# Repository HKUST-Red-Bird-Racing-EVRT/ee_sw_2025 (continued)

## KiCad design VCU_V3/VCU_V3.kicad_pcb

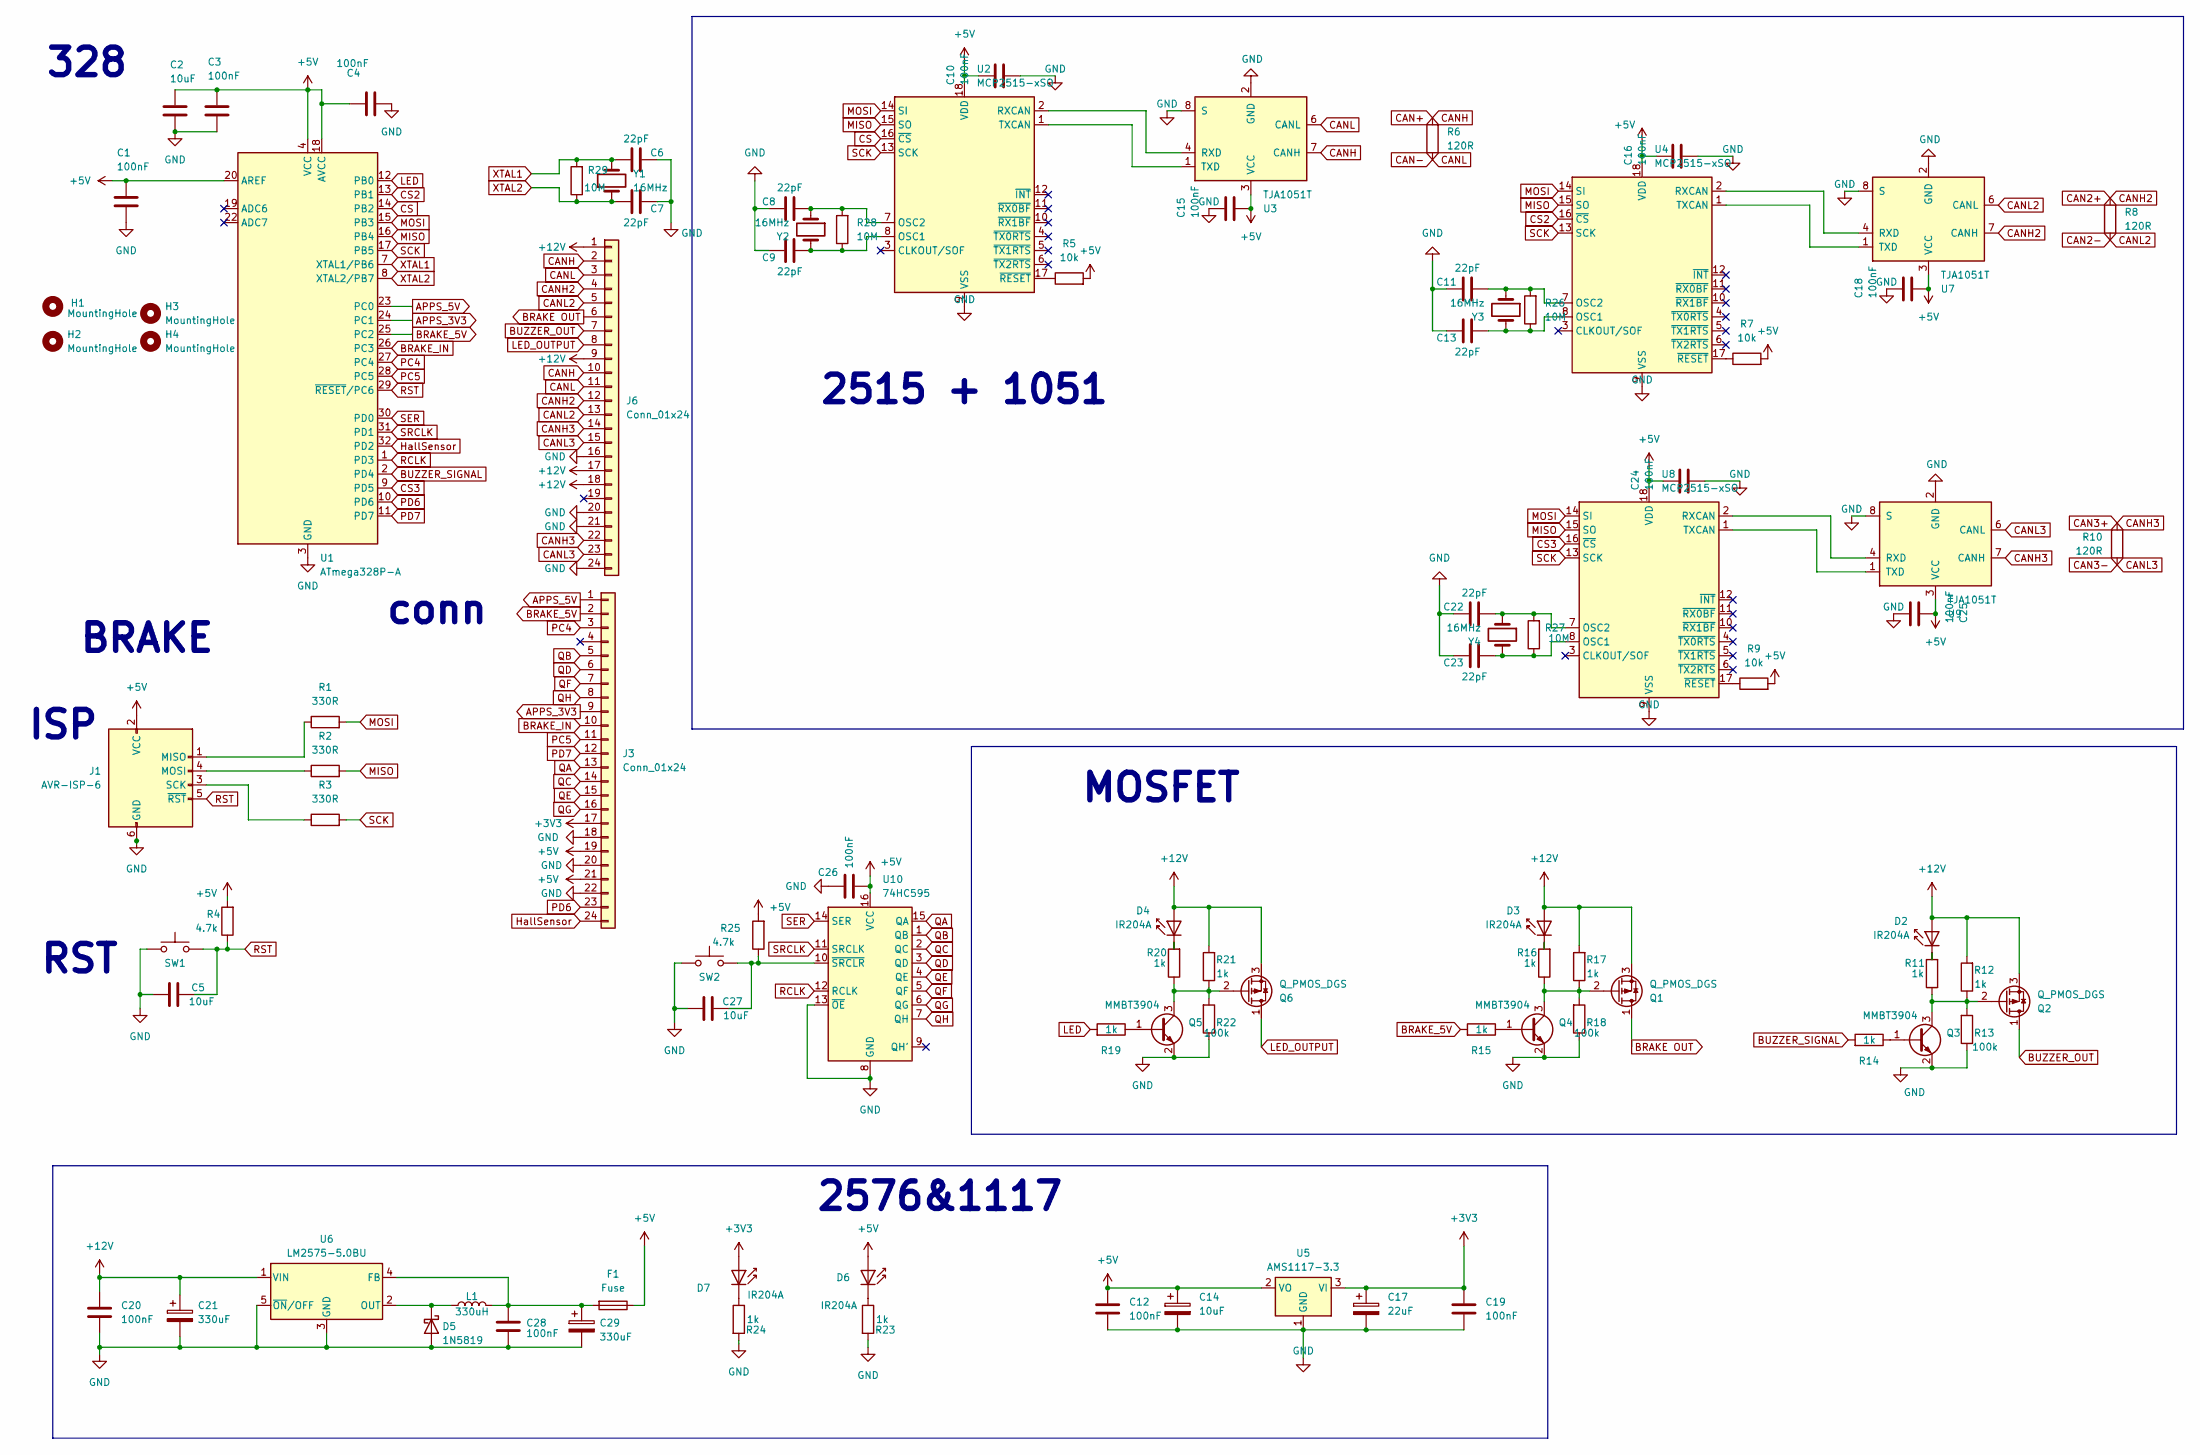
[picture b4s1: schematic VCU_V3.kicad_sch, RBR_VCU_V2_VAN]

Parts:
C1, C3, C4, C10, C12, C15, C16, C18, C19, C20, C24, C25, C26, C28: 100nF; C_0805_2012Metric_Pad1.18x1.45mm_HandSolder_L
C2, C5, C14, C27: 10uF; C_0805_2012Metric_Pad1.18x1.45mm_HandSolder_L
C6, C7, C8, C9, C11, C13, C22, C23: 22pF; C_0805_2012Metric_Pad1.18x1.45mm_HandSolder_L
C17: 22uF; C_0805_2012Metric_Pad1.18x1.45mm_HandSolder_L
C21, C29: 330uF; CP_Radial_D10.0mm_P5.00mm_F
D2, D3, D4, D6, D7: IR204A; LED_1206_3216Metric_Pad1.42x1.75mm_HandSolder
D5: 1N5819; D_SMA_Handsoldering
F1: Fuse; Fuse_1210_3225Metric_Pad1.42x2.65mm_HandSolder
H1, H2, H3, H4: MountingHole; MountingHole_3.2mm_M3
J1: AVR-ISP-6; PinHeader_2x03_P2.54mm_Vertical
J3, J6: Conn_01x24; HD241_24pin
L1: 330uH; L_10.4x10.4_H4.8
Q1, Q2, Q6: Q_PMOS_DGS; SOT-23
Q3, Q4, Q5: MMBT3904; SOT-23
R1, R2, R3: 330R; R_0805_2012Metric_Pad1.20x1.40mm_HandSolder_L
R4, R25: 4.7k; R_0805_2012Metric_Pad1.20x1.40mm_HandSolder_L
R5, R7, R9: 10k; R_0805_2012Metric_Pad1.20x1.40mm_HandSolder_L
R6, R8, R10: 120R; R_0805_2012Metric_Pad1.20x1.40mm_HandSolder_L
R11, R12, R14, R15, R16, R17, R19, R20, R21, R23, R24: 1k; R_0805_2012Metric_Pad1.20x1.40mm_HandSolder_L
R13, R18, R22: 100k; R_0805_2012Metric_Pad1.20x1.40mm_HandSolder_L
R26, R27, R28, R29: 10M; R_0805_2012Metric_Pad1.20x1.40mm_HandSolder_L
SW1, SW2: SW_Push; SW_PUSH_6mm_H5mm
U1: ATmega328P-A; TQFP-32_7x7mm_P0.8mm_L
U2, U4, U8: MCP2515-xSO; SOIC-18W_7.5x11.6mm_P1.27mm_L
U3, U7, U9: TJA1051T; SOIC-8_3.9x4.9mm_P1.27mm
U5: AMS1117-3.3; SOT-223-3_TabPin2
U6: LM2575-5.0BU; TO-263-5_TabPin3
U10: 74HC595; SOIC-16_3.9x9.9mm_P1.27mm
Y1, Y2, Y3, Y4: 16MHz; Crystal_HC49-U_Vertical_W_SMD

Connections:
+3V3: C17.1, C19.1, D7.2 (A), J3.17, U5.3 (VI)
+5V: C1.2, C2.2, C3.2, C4.2, C10.2, C12.1, C14.1, C15.1, C16.2, C18.1, C24.2, C25.2, C26.1, D6.2 (A), F1.1, J1.2 (VCC), J3.19, J3.21, R4.2, R5.2, R7.2, R9.2, R25.2, U1.4 (VCC), U1.6 (VCC), U1.18 (AVCC), U1.20 (AREF), U2.18 (VDD), U3.3 (VCC), U4.18 (VDD), U5.2 (VO), U7.3 (VCC), U8.18 (VDD), U9.3 (VCC), U10.16 (VCC)
+12V: C20.1, C21.1, D2.2 (A), D3.2 (A), D4.2 (A), J6.1, J6.9, J6.17, J6.18, Q1.3 (S), Q2.3 (S), Q6.3 (S), R12.2, R17.2, R21.2, U6.1 (VIN)
APPS_3V3: J3.9, U1.24 (PC1)
APPS_5V: J3.1, U1.23 (PC0)
BRAKE OUT: J6.6, Q1.1 (D)
BRAKE_5V: J3.2, R15.2, U1.25 (PC2)
BRAKE_IN: J3.10, U1.26 (PC3)
BUZZER_OUT: J6.7, Q2.1 (D)
BUZZER_SIGNAL: R14.2, U1.2 (PD4)
CAN2+: J6.4, J6.12, R8.2, U7.7 (CANH)
CAN2-: J6.5, J6.13, R8.1, U7.6 (CANL)
CAN3+: J6.14, J6.22, R10.2, U9.7 (CANH)
CAN3-: J6.15, J6.23, R10.1, U9.6 (CANL)
CAN+: J6.2, J6.10, R6.2, U3.7 (CANH)
CAN-: J6.3, J6.11, R6.1, U3.6 (CANL)
CS: U1.14 (PB2), U2.16 (~CS)
CS2: U1.13 (PB1), U4.16 (~CS)
CS3: U1.9 (PD5), U8.16 (~CS)
GND: C1.1, C2.1, C3.1, C4.1, C5.1, C6.1, C7.1, C8.1, C9.1, C10.1, C11.1, C12.2, C13.1, C14.2, C15.2, C16.1, C17.2, C18.2, C19.2, C20.2, C21.2, C22.1, C23.1, C24.1, C25.1, C26.2, C27.1, C28.2, C29.2, D5.2 (A), J1.6 (GND), J3.18, J3.20, J3.22, J6.16, J6.20, J6.21, J6.24, Q3.2 (E), Q4.2 (E), Q5.2 (E), R13.1, R18.1, R22.1, R23.2, R24.2, SW1.1, SW2.1, U1.3 (GND), U1.5 (GND), U1.21 (GND), U2.9 (VSS), U3.2 (GND), U3.8 (S), U4.9 (VSS), U5.1 (GND), U6.3 (GND), U6.5 (~ON/OFF), U7.2 (GND), U7.8 (S), U8.9 (VSS), U9.2 (GND), U9.8 (S), U10.8 (GND), U10.13 (~OE)
HallSensor: J3.24, U1.32 (PD2)
LED: R19.2, U1.12 (PB0)
LED_OUTPUT: J6.8, Q6.1 (D)
MISO: R2.2, U1.16 (PB4), U2.15 (SO), U4.15 (SO), U8.15 (SO)
MOSI: R1.2, U1.15 (PB3), U2.14 (SI), U4.14 (SI), U8.14 (SI)
unnamed: D2.1 (K), R11.2
unnamed: D3.1 (K), R16.2
unnamed: D4.1 (K), R20.2
unnamed: D5.1 (K), L1.1, U6.2 (OUT)
unnamed: D6.1 (K), R23.1
unnamed: D7.1 (K), R24.1
unnamed: J1.1 (MISO), R1.1
unnamed: J1.4 (MOSI), R2.1
unnamed: J1.3 (SCK), R3.1
unnamed: Q1.2 (G), Q4.3 (C), R16.1, R17.1, R18.2
unnamed: Q2.2 (G), Q3.3 (C), R11.1, R12.1, R13.2
unnamed: Q3.1 (B), R14.1
unnamed: Q4.1 (B), R15.1
unnamed: Q5.1 (B), R19.1
unnamed: Q5.3 (C), Q6.2 (G), R20.1, R21.1, R22.2
unnamed: C9.2, R28.1, U2.8 (OSC1), Y2.2
unnamed: C8.2, R28.2, U2.7 (OSC2), Y2.1
unnamed: U2.2 (RXCAN), U3.4 (RXD)
unnamed: U2.1 (TXCAN), U3.1 (TXD)
unnamed: R5.1, U2.17 (~RESET)
unnamed: C13.2, R26.1, U4.8 (OSC1), Y3.2
unnamed: C11.2, R26.2, U4.7 (OSC2), Y3.1
unnamed: U4.2 (RXCAN), U7.4 (RXD)
unnamed: U4.1 (TXCAN), U7.1 (TXD)
unnamed: R7.1, U4.17 (~RESET)
unnamed: C28.1, C29.1, F1.2, L1.2, U6.4 (FB)
unnamed: C23.2, R27.1, U8.8 (OSC1), Y4.2
unnamed: C22.2, R27.2, U8.7 (OSC2), Y4.1
unnamed: U8.2 (RXCAN), U9.4 (RXD)
unnamed: U8.1 (TXCAN), U9.1 (TXD)
unnamed: R9.1, U8.17 (~RESET)
unnamed: C27.2, R25.1, SW2.2, U10.10 (~SRCLR)
PC4: J3.3, U1.27 (PC4)
PC5: J3.11, U1.28 (PC5)
PD6: J3.23, U1.10 (PD6)
PD7: J3.12, U1.11 (PD7)
QA: J3.13, U10.15 (QA)
QB: J3.5, U10.1 (QB)
QC: J3.14, U10.2 (QC)
QD: J3.6, U10.3 (QD)
QE: J3.15, U10.4 (QE)
QF: J3.7, U10.5 (QF)
QG: J3.16, U10.6 (QG)
QH: J3.8, U10.7 (QH)
RCLK: U1.1 (PD3), U10.12 (RCLK)
RST: C5.2, J1.5 (~RST), R4.1, SW1.2, U1.29 (~RESET/PC6)
SCK: R3.2, U1.17 (PB5), U2.13 (SCK), U4.13 (SCK), U8.13 (SCK)
SER: U1.30 (PD0), U10.14 (SER)
SRCLK: U1.31 (PD1), U10.11 (SRCLK)
XTAL1: C6.2, R29.2, U1.7 (XTAL1/PB6), Y1.2
XTAL2: C7.2, R29.1, U1.8 (XTAL2/PB7), Y1.1

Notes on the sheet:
RST
conn
ISP
2576&1117
MOSFET
2515 + 1051
BRAKE
328

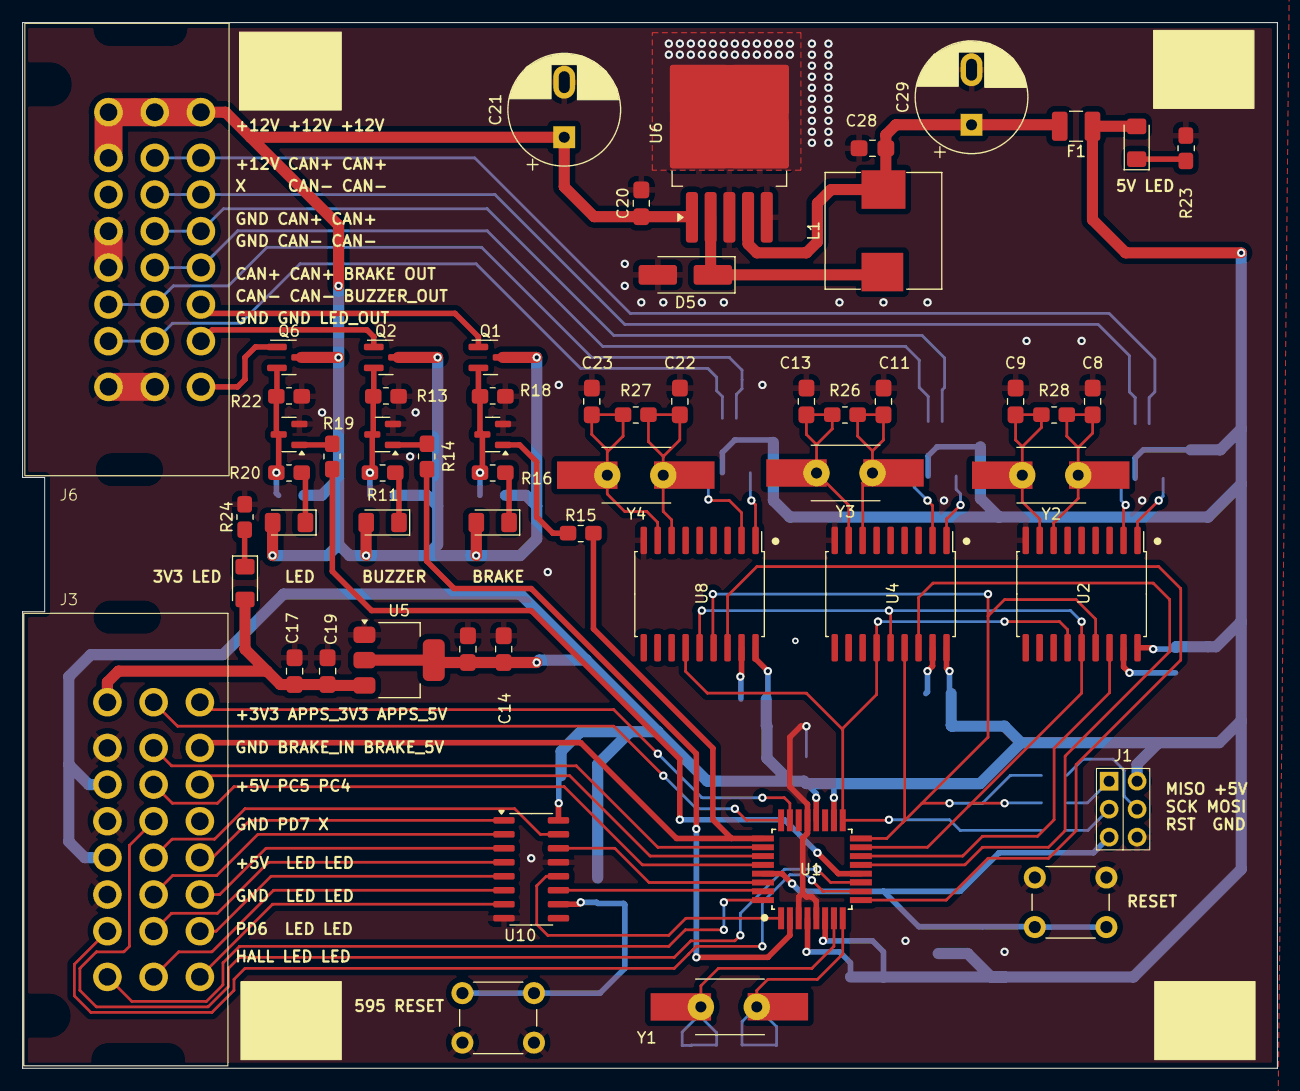
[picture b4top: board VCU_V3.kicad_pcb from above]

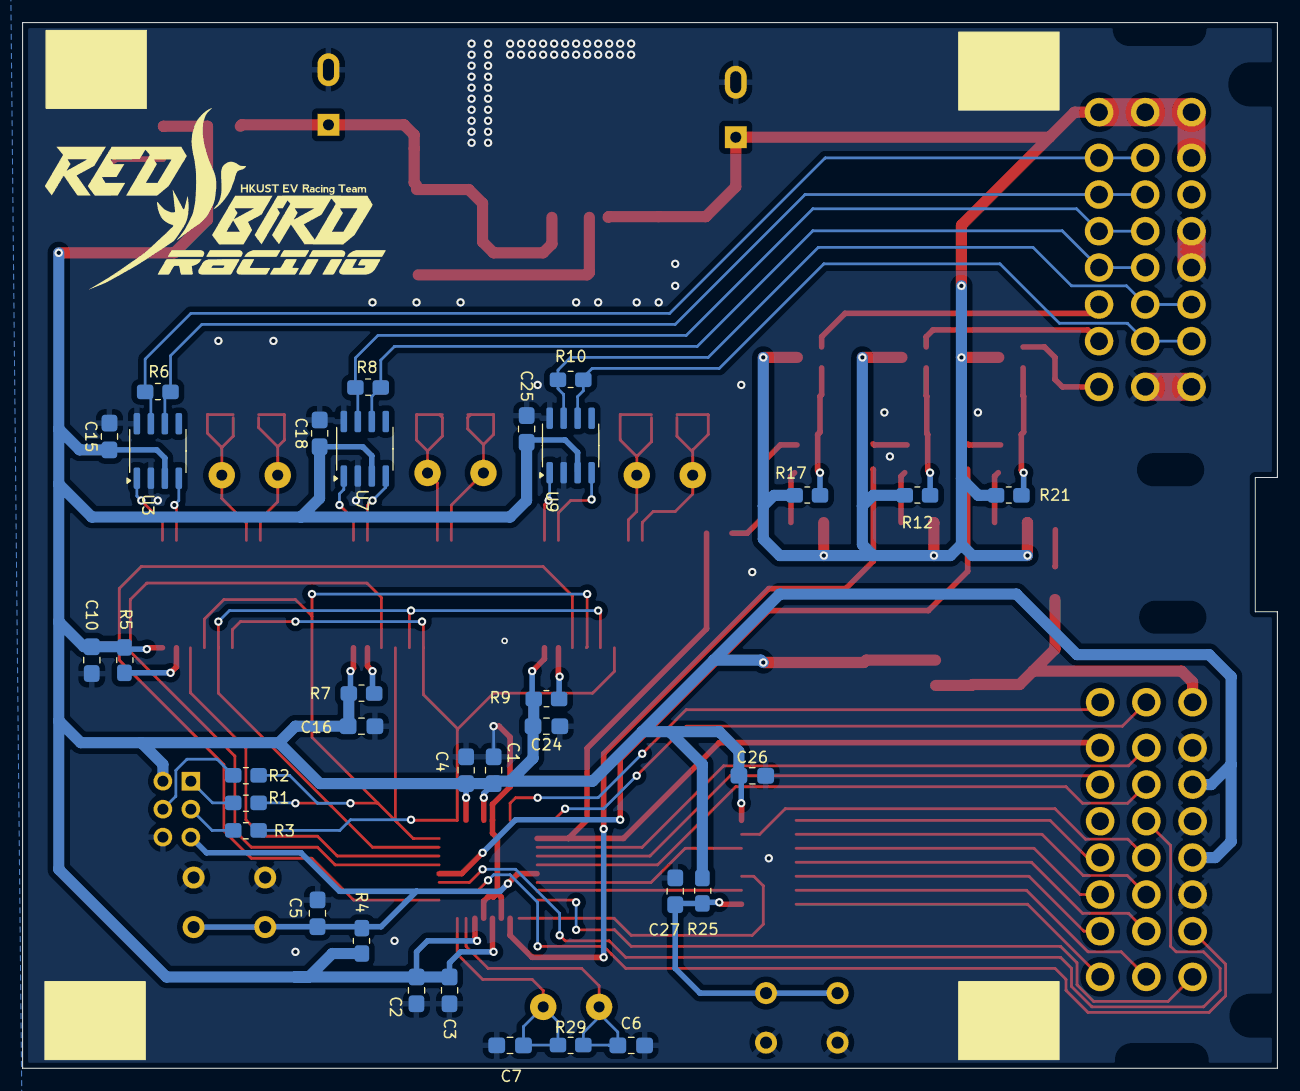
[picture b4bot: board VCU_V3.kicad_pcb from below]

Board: 2 copper layers, 114.0 x 95.0 mm, 95 parts (33 on the bottom side), 76 nets.

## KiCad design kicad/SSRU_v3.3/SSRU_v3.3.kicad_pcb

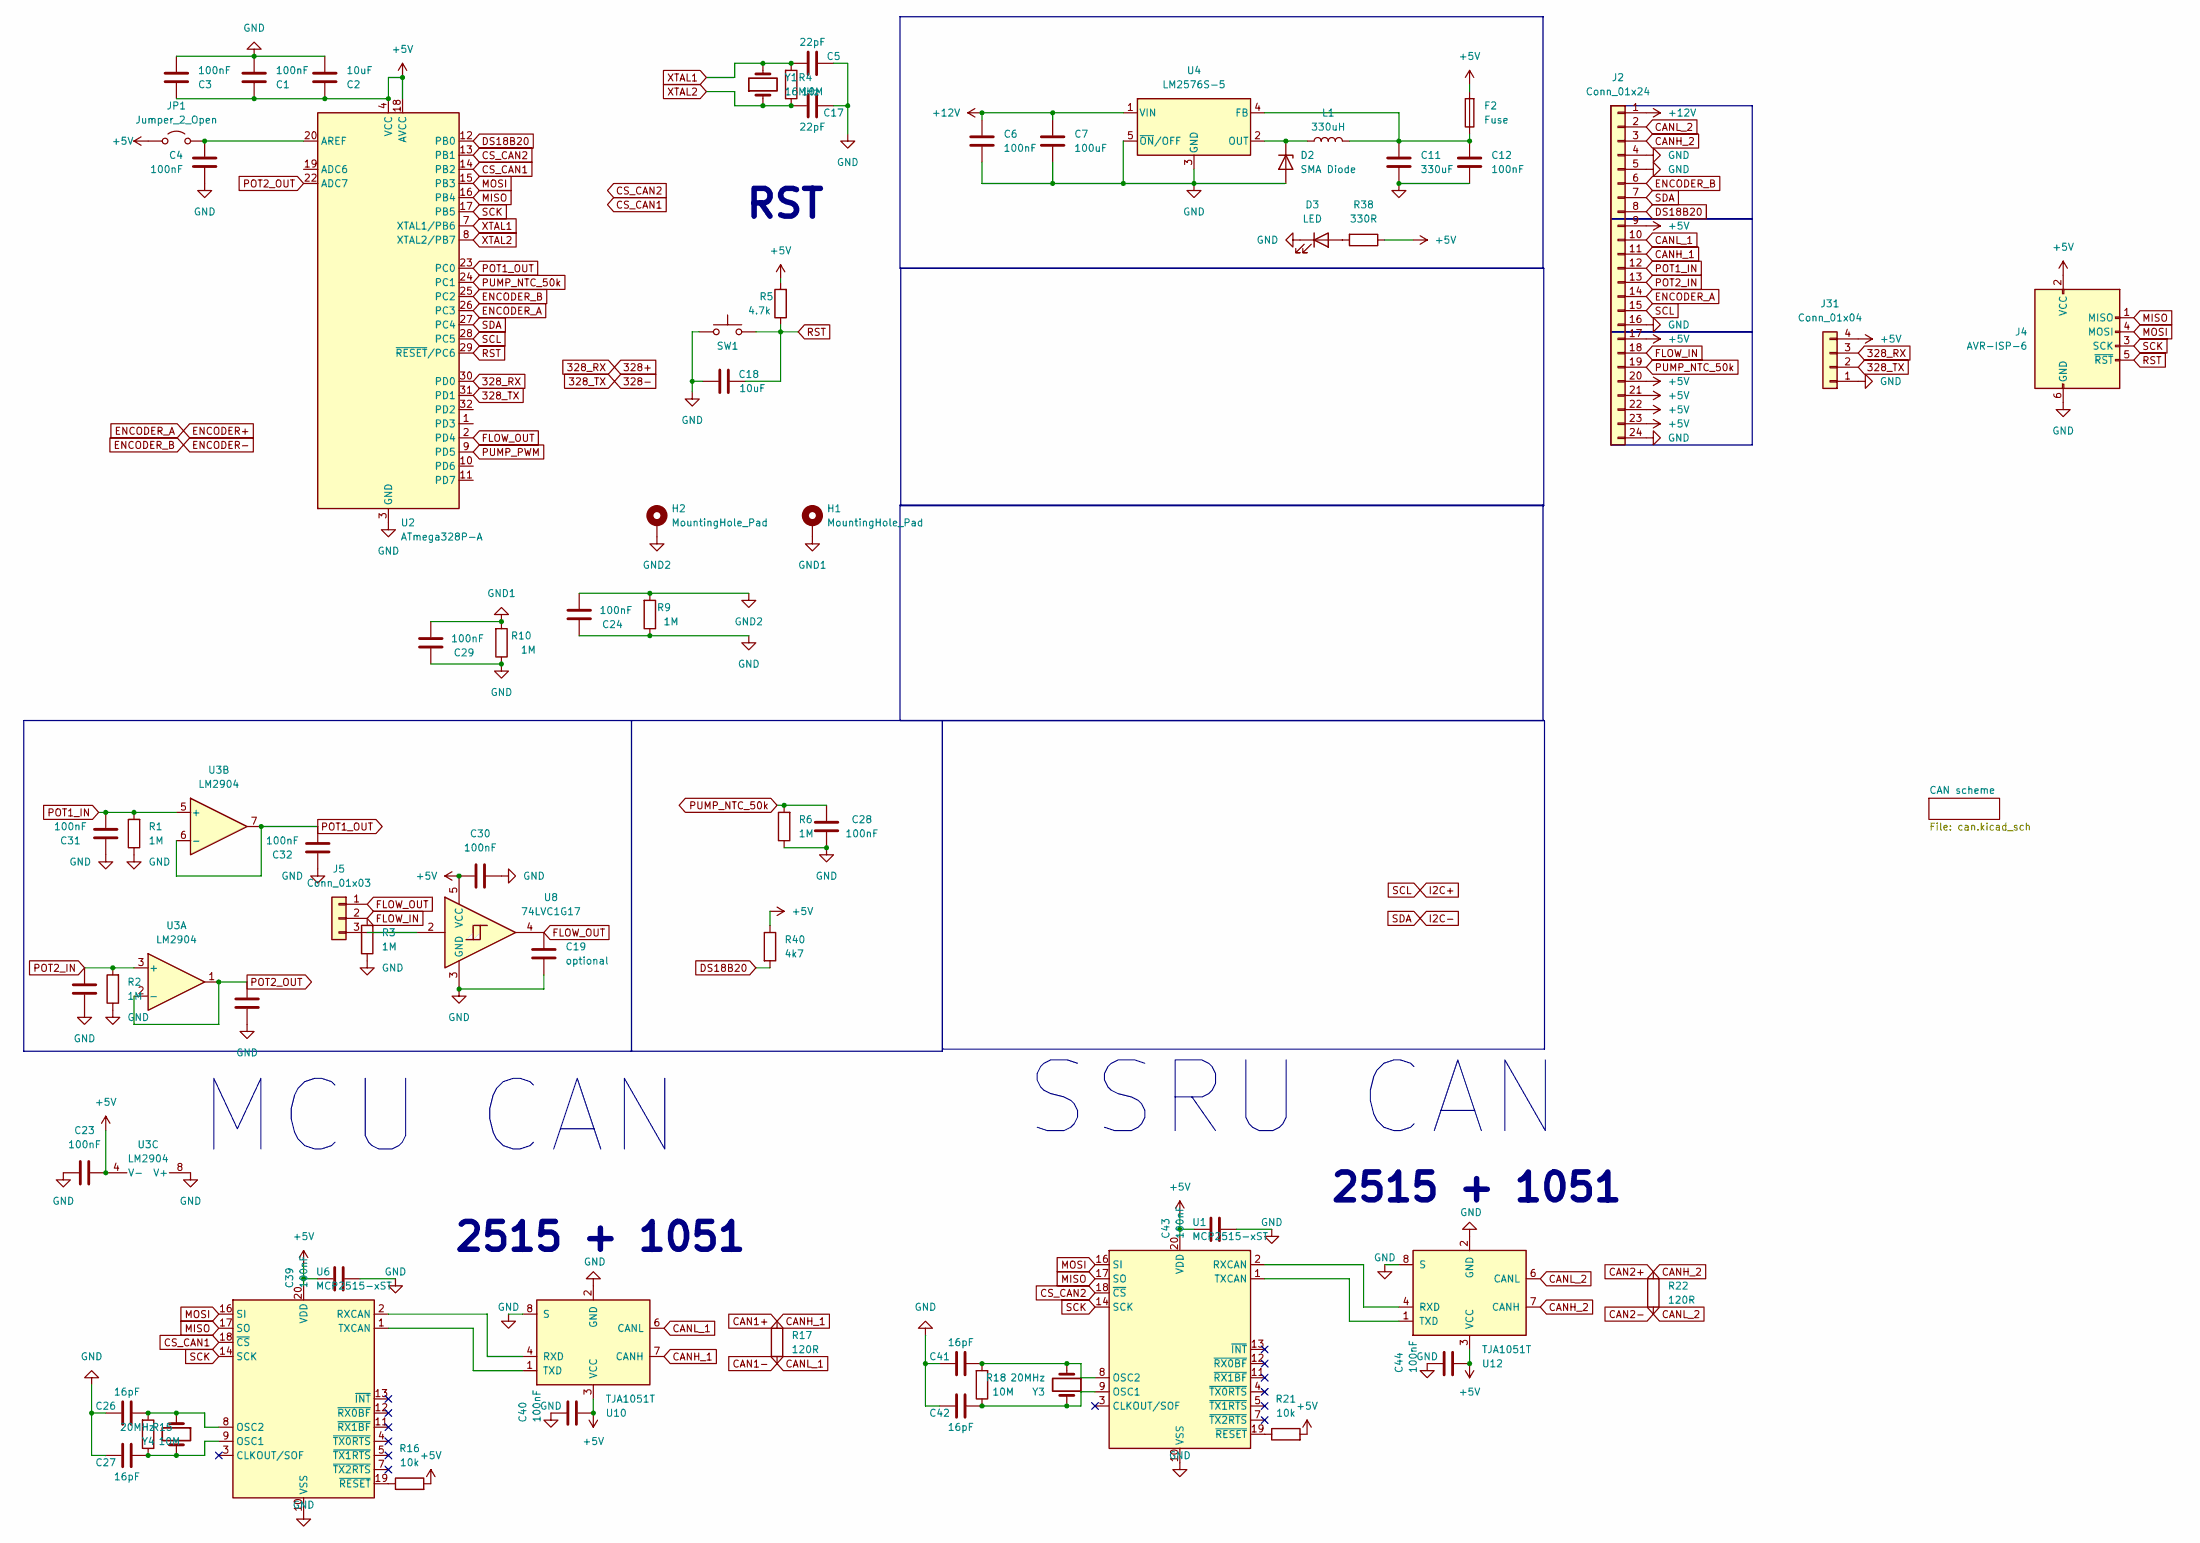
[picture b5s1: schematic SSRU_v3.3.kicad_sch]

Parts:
C1, C3, C4, C6, C12, C23, C24, C28, C29, C30, C31, C32, C36, C37, C39, C40, C43, C44: 100nF; C_0805_2012Metric_Pad1.18x1.45mm_HandSolder_L
C2, C18: 10uF; C_0805_2012Metric_Pad1.18x1.45mm_HandSolder_L
C5, C17: 22pF; C_0805_2012Metric_Pad1.18x1.45mm_HandSolder_L
C7: 100uF; CP_Radial_D6.3mm_P2.50mm_handsolder
C11: 330uF; CP_Radial_D6.3mm_P2.50mm_handsolder
C19: optional; C_0805_2012Metric_Pad1.18x1.45mm_HandSolder_L
C26, C27, C41, C42: 16pF; C_0805_2012Metric_Pad1.18x1.45mm_HandSolder_L
D2: SMA Diode; D_SMA_Handsoldering
D3: LED; LED_0805_2012Metric_Pad1.45x1.40mm_HandSolder
F2: Fuse; Fuse_1210_3225Metric_Pad1.42x2.65mm_HandSolder
H1: MountingHole_Pad; MountingHole_3.2mm_M3_Pad_TopBottom
H2: MountingHole_Pad; MountingHole_3.5mm_Pad_TopBottom
J2: Conn_01x24; HD241_24pin
J4: AVR-ISP-6; PinHeader_2x03_P2.54mm_Vertical
J5: Conn_01x03; SolderJumper-3_P1.3mm_Open_Pad1.0x1.5mm
J31: Conn_01x04; JST_XH_B4B-XH-A_1x04_P2.50mm_Vertical
JP1: Jumper_2_Open; SolderJumper-2_P1.3mm_Open_Pad1.0x1.5mm
L1: 330uH; L_10.4x10.4_H4.8
R1, R2, R3, R6, R9, R10: 1M; R_0805_2012Metric_Pad1.20x1.40mm_HandSolder_L
R4, R15, R18: 10M; R_0805_2012Metric_Pad1.20x1.40mm_HandSolder_L
R5: 4.7k; R_0805_2012Metric_Pad1.20x1.40mm_HandSolder_L
R16, R21: 10k; R_0805_2012Metric_Pad1.20x1.40mm_HandSolder_L
R17, R22: 120R; R_0805_2012Metric_Pad1.20x1.40mm_HandSolder_L
R38: 330R; R_0805_2012Metric_Pad1.20x1.40mm_HandSolder_L
R40: 4k7; R_0805_2012Metric_Pad1.20x1.40mm_HandSolder_L
SW1: SW_Push; SW_PUSH_6mm_H5mm
U1, U6: MCP2515-xST; TSSOP-20_4.4x6.5mm_P0.65mm
U2: ATmega328P-A; TQFP-32_7x7mm_P0.8mm_L
U3: LM2904; SOIC-8_3.9x4.9mm_P1.27mm_RMC_Handsolder
U4: LM2576S-5; TO-263-5_TabPin3_Handsolder
U8: 74LVC1G17; SOT-23-5_HandSoldering_Extended_RMC
U10, U12: TJA1051T; SOIC-8_3.9x4.9mm_P1.27mm_RMC_Handsolder
Y1: 16MHz; Crystal_HC49-U_Vertical_W_SMD
Y3, Y4: 20MHz; Crystal_HC49-U_Vertical_W_SMD

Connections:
328+: J31.3, U2.30 (PD0)
328-: J31.2, U2.31 (PD1)
+5V: C1.2, C2.2, C3.2, C23.2, C30.2, C39.2, C40.1, C43.2, C44.1, F2.2, J2.9, J2.17, J2.20, J2.21, J2.22, J2.23, J4.2 (VCC), J31.4, JP1.1 (A), R5.2, R16.2, R21.2, R38.1, R40.1, U1.20 (VDD), U2.4 (VCC), U2.6 (VCC), U2.18 (AVCC), U3.4 (V-), U6.20 (VDD), U8.5 (VCC), U10.3 (VCC), U12.3 (VCC)
+12V: C6.2, C7.1, J2.1, U4.1 (VIN)
CAN1+: J2.11, R17.2, U10.7 (CANH)
CAN1-: J2.10, R17.1, U10.6 (CANL)
CAN2+: J2.3, R22.2, U12.7 (CANH)
CAN2-: J2.2, R22.1, U12.6 (CANL)
CS_CAN1: U2.14 (PB2), U6.18 (~CS)
CS_CAN2: U1.18 (~CS), U2.13 (PB1)
DS18B20: J2.8, R40.2, U2.12 (PB0)
ENCODER+: J2.14, U2.26 (PC3)
ENCODER-: J2.6, U2.25 (PC2)
FLOW_IN: J2.18, J5.2, R3.2
FLOW_OUT: C19.2, J5.1, U2.2 (PD4), U8.4
GND: C1.1, C2.1, C3.1, C4.1, C5.1, C6.1, C7.2, C11.2, C12.1, C17.1, C18.1, C19.1, C23.1, C24.1, C26.1, C27.1, C28.2, C29.1, C30.1, C31.1, C32.1, C36.1, C37.1, C39.1, C40.2, C41.1, C42.1, C43.1, C44.2, D2.2 (A), D3.1 (K), J2.4, J2.5, J2.16, J2.24, J4.6 (GND), J31.1, R1.1, R2.1, R3.1, R6.1, R9.1, R10.1, SW1.1, U1.10 (VSS), U2.3 (GND), U2.5 (GND), U2.21 (GND), U3.8 (V+), U4.3 (GND), U4.5 (~ON/OFF), U6.10 (VSS), U8.3 (GND), U10.2 (GND), U10.8 (S), U12.2 (GND), U12.8 (S)
GND1: C29.2, H1.1, R10.2
GND2: C24.2, H2.1, R9.2
I2C+: J2.15, U2.28 (PC5)
I2C-: J2.7, U2.27 (PC4)
MISO: J4.1 (MISO), U1.17 (SO), U2.16 (PB4), U6.17 (SO)
MOSI: J4.4 (MOSI), U1.16 (SI), U2.15 (PB3), U6.16 (SI)
unnamed: D2.1 (K), L1.1, U4.2 (OUT)
unnamed: D3.2 (A), R38.2
unnamed: J5.3, U8.2
unnamed: C4.2, JP1.2 (B), U2.20 (AREF)
unnamed: C42.2, R18.1, U1.9 (OSC1), Y3.2
unnamed: C41.2, R18.2, U1.8 (OSC2), Y3.1
unnamed: U1.2 (RXCAN), U12.4 (RXD)
unnamed: U1.1 (TXCAN), U12.1 (TXD)
unnamed: R21.1, U1.19 (~RESET)
unnamed: C11.1, C12.2, F2.1, L1.2, U4.4 (FB)
unnamed: C27.2, R15.1, U6.9 (OSC1), Y4.2
unnamed: C26.2, R15.2, U6.8 (OSC2), Y4.1
unnamed: R16.1, U6.19 (~RESET)
unnamed: U6.2 (RXCAN), U10.4 (RXD)
unnamed: U6.1 (TXCAN), U10.1 (TXD)
POT1_IN: C31.2, J2.12, R1.2, U3.5 (+)
POT1_OUT: C32.2, U2.23 (PC0), U3.6 (-), U3.7
POT2_IN: C36.2, J2.13, R2.2, U3.3 (+)
POT2_OUT: C37.2, U2.22 (ADC7), U3.1, U3.2 (-)
PUMP_NTC_50k: C28.1, J2.19, R6.2, U2.24 (PC1)
PUMP_PWM: U2.9 (PD5)
RST: C18.2, J4.5 (~RST), R5.1, SW1.2, U2.29 (~RESET/PC6)
SCK: J4.3 (SCK), U1.14 (SCK), U2.17 (PB5), U6.14 (SCK)
XTAL1: C5.2, R4.2, U2.7 (XTAL1/PB6), Y1.2
XTAL2: C17.2, R4.1, U2.8 (XTAL2/PB7), Y1.1

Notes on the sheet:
MCU CAN
2515 + 1051
RST
SSRU CAN

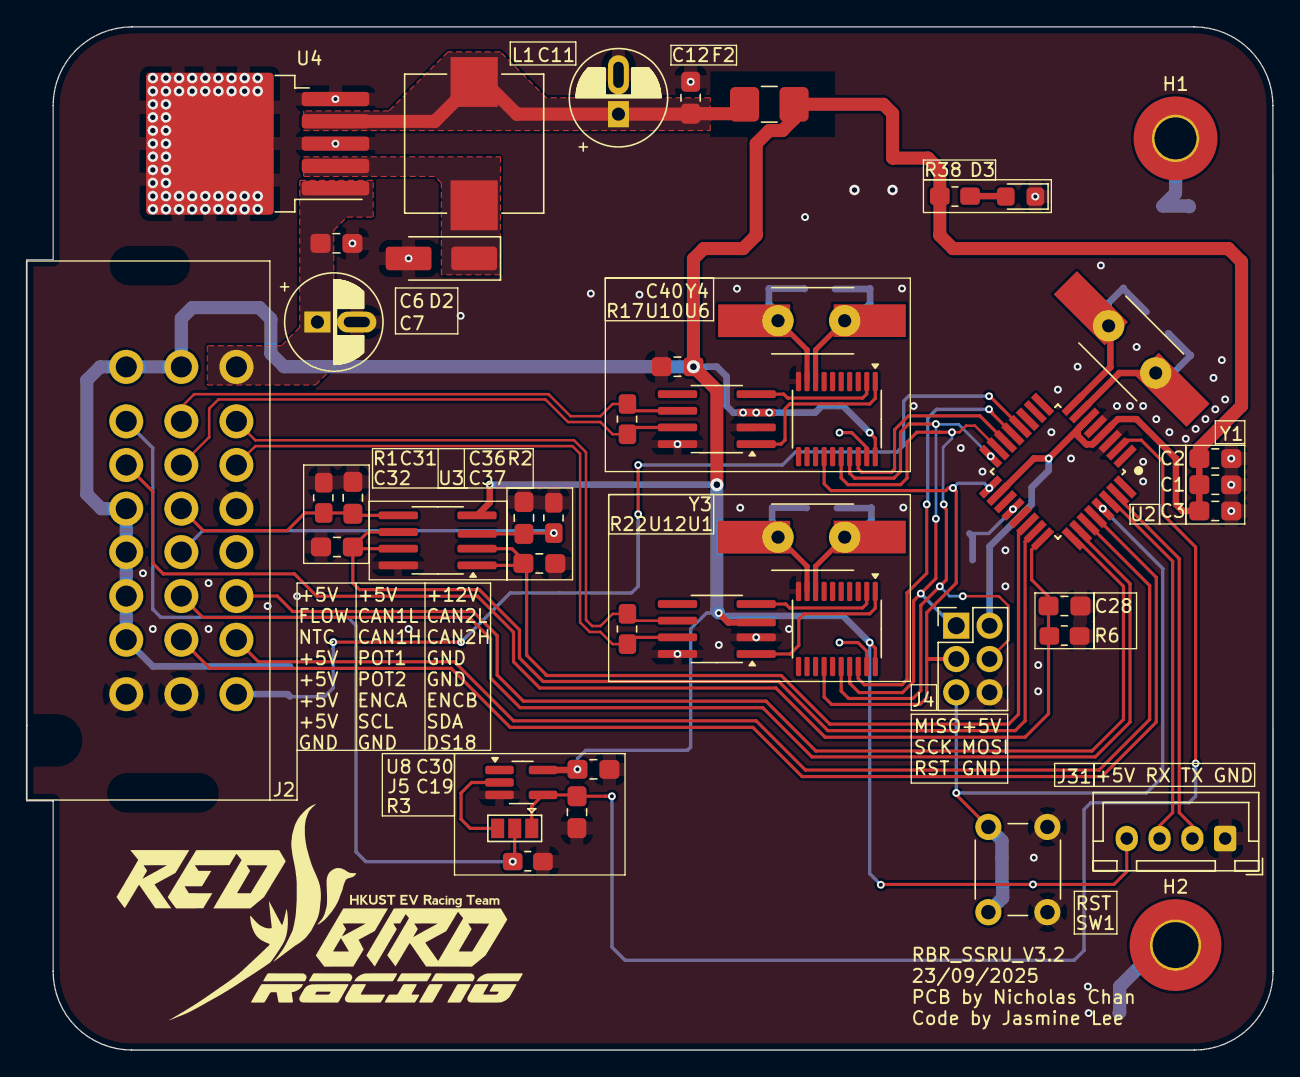
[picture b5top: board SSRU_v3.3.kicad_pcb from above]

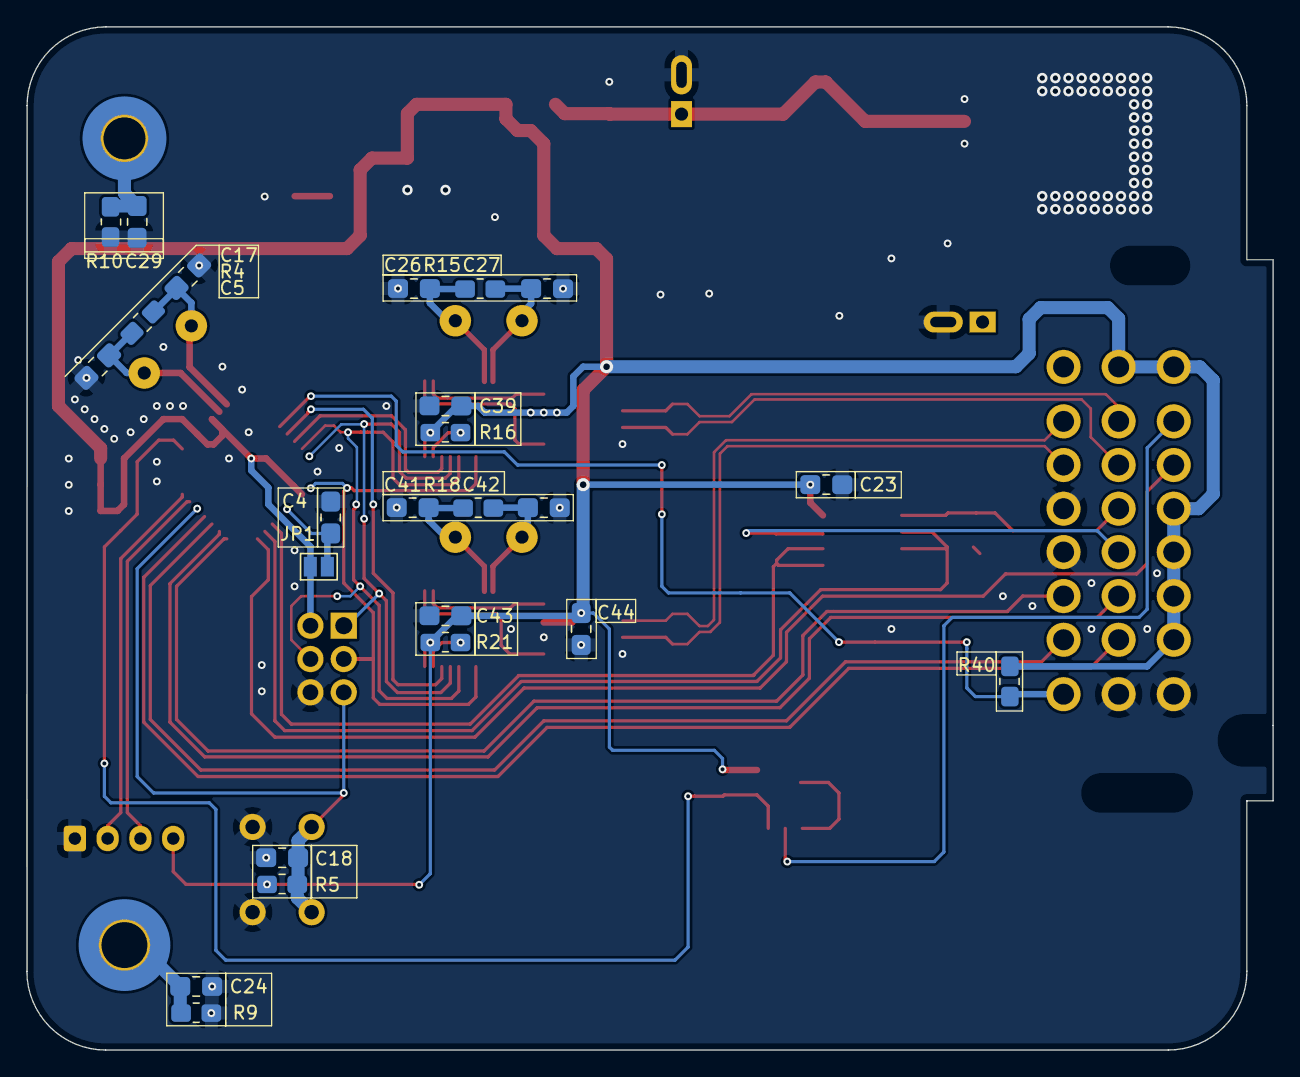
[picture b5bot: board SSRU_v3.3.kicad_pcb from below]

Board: 2 copper layers, 95.0 x 78.0 mm, 68 parts (24 on the bottom side), 46 nets.
